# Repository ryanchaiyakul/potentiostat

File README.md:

# Potentiostat

I2BL potentiostat library and project.

# Goals

1. Create a library to easily program simple potentiostats for various voltammetry methods.
2. Create a collection of tools to develop future potentiostats.
3. Create a simulation suite to visualize and validate design decisions.

# Simulations

Go to the [README.md](CAD/LTSpice/README.md) in CAD/LTSpice folder.

# Tools

Go to the tools folder for a complete collection.

## CPE Models

Generate RC Train models of CPE elements to simulate how the readout circuit responds.

## PWL Voltammetry

Generate PWL files to pass into a voltage source to act as the DAC.

# Usage

```bash
# submodules are used in this repository for third party libraries
git clone --recurse-submodules git@github.com:ryanchaiyakul/potentiostat.git
```

1. Open the project in [VS Code](https://code.visualstudio.com/) with the [PlatformIO extension](https://marketplace.visualstudio.com/items?itemName=platformio.platformio-ide) installed.
2. Connect the Potentiostat to your computer by USB.
3. Navigate to the PlatformIO panel and click "Upload" or use the Command Palette (CNTL + SHIFT + P) and select "Upload".
4. Use the Serial Monitor in the terminal bar and select the baudrate of 230400.

# Features

- [x] Differential Pulse Voltammetry
- [x] Square Wave Voltammetry
- [ ] Cyclic Voltammetry
- [x] 300+ Hz SWV
- [ ] OTA Configuration
- [ ] EEPROM Persistent Configuration
- [ ] BLE Integration
- [x] Simple "Debug" Mode
- [x] Complete Analytics in "Debug" Mode
- [ ] Unit Testing Suite

# Development Guide

Create a valid class that inherits from Voltammetry defined in [Voltammetry.h](lib/Voltammetry/Voltammetry.h).

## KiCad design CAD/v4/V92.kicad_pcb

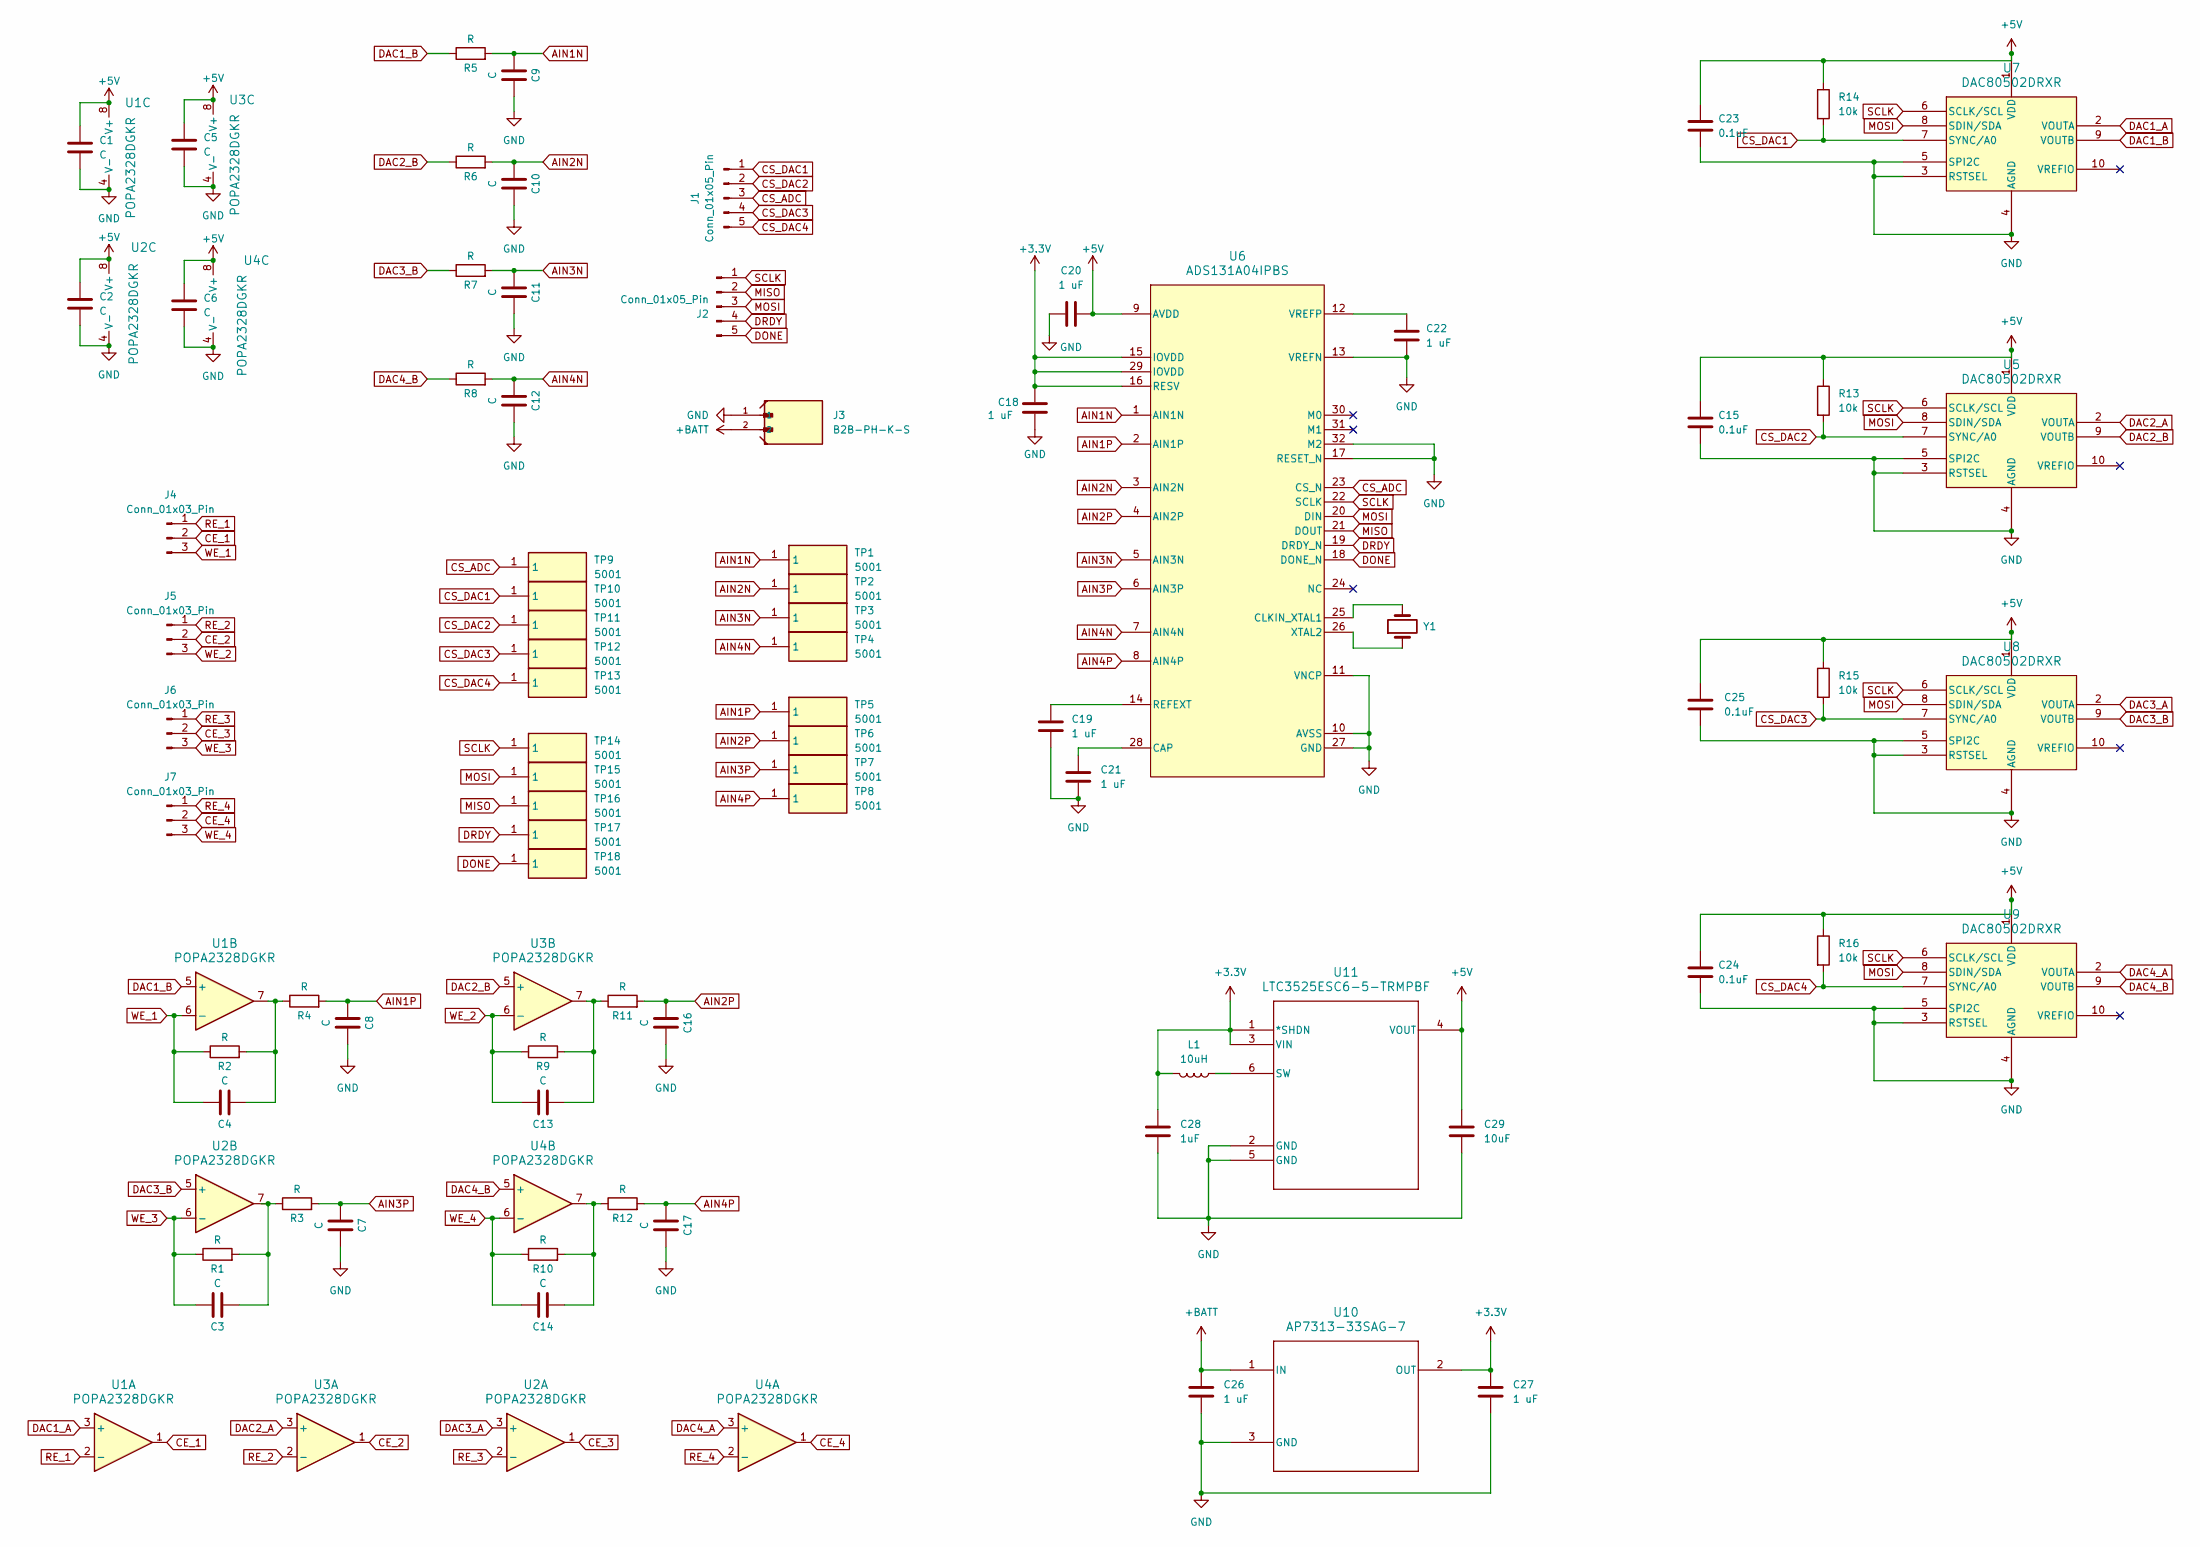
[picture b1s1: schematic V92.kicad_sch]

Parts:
C1, C2, C3, C4, C5, C6, C7, C8, C9, C10, C11, C12, C13, C14, C16, C17: C; C_0603_1608Metric_Pad1.08x0.95mm_HandSolder
C15, C23, C24, C25: 0.1uF; C_0603_1608Metric_Pad1.08x0.95mm_HandSolder
C18, C19, C20, C21, C22, C26, C27: 1 uF; C_0603_1608Metric_Pad1.08x0.95mm_HandSolder
C28: 1uF; C_0603_1608Metric_Pad1.08x0.95mm_HandSolder
C29: 10uF; C_0603_1608Metric_Pad1.08x0.95mm_HandSolder
J1, J2: Conn_01x05_Pin; PinHeader_1x05_P2.54mm_Vertical
J3: B2B-PH-K-S; JST_B2B-PH-K-S
J4, J5, J6, J7: Conn_01x03_Pin; PinHeader_1x03_P2.54mm_Vertical
L1: 10uH; L_0603_1608Metric_Pad1.05x0.95mm_HandSolder
R1, R2, R3, R4, R5, R6, R7, R8, R9, R10, R11, R12: R; R_0603_1608Metric_Pad0.98x0.95mm_HandSolder
R13, R14, R15, R16: 10k; R_0603_1608Metric_Pad0.98x0.95mm_HandSolder
TP1, TP2, TP3, TP4, TP5, TP6, TP7, TP8, TP9, TP10, TP11, TP12, TP13, TP14, TP15, TP16, TP17, TP18: 5001; 5000; Mouser Part Number 534-5001
U1, U2, U3, U4: POPA2328DGKR; SO8_DGK_TEX
U5, U7, U8, U9: DAC80502DRXR; SON_02DRXR_TEX
U6: ADS131A04IPBS; PBS0032A_N
U10: AP7313-33SAG-7; SOT-23_DIO
U11: LTC3525ESC6-5-TRMPBF; SC70-SC6_LIT
Y1: Crystal; Crystal_SMD_HC49-SD

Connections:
+3.3V: C18.1, C27.1, C28.1, L1.2, U6.15 (IOVDD), U6.16 (RESV), U6.29 (IOVDD), U10.2 (OUT), U11.1 (*SHDN), U11.3 (VIN)
+5V: C1.1, C2.1, C5.1, C6.1, C15.1, C20.1, C23.1, C24.1, C25.1, C29.1, R13.1, R14.1, R15.1, R16.1, U1.8 (V+), U2.8 (V+), U3.8 (V+), U4.8 (V+), U5.1 (VDD), U6.9 (AVDD), U7.1 (VDD), U8.1 (VDD), U9.1 (VDD), U11.4 (VOUT)
+BATT: C26.1, J3.2, U10.1 (IN)
AIN1N: C9.2, R5.2, TP1.1, U6.1 (AIN1N)
AIN1P: C8.2, R4.2, TP5.1, U6.2 (AIN1P)
AIN2N: C10.2, R6.2, TP2.1, U6.3 (AIN2N)
AIN2P: C16.2, R11.2, TP6.1, U6.4 (AIN2P)
AIN3N: C11.2, R7.2, TP3.1, U6.5 (AIN3N)
AIN3P: C7.2, R3.2, TP7.1, U6.6 (AIN3P)
AIN4N: C12.2, R8.2, TP4.1, U6.7 (AIN4N)
AIN4P: C17.2, R12.2, TP8.1, U6.8 (AIN4P)
CE_1: J4.2, U1.1
CE_2: J5.2, U3.1
CE_3: J6.2, U2.1
CE_4: J7.2, U4.1
CS_ADC: J1.3, TP9.1, U6.23 (CS_N)
CS_DAC1: J1.1, R14.2, TP10.1, U7.7 (SYNC/A0)
CS_DAC2: J1.2, R13.2, TP11.1, U5.7 (SYNC/A0)
CS_DAC3: J1.4, R15.2, TP12.1, U8.7 (SYNC/A0)
CS_DAC4: J1.5, R16.2, TP13.1, U9.7 (SYNC/A0)
DAC1_A: U1.3 (+), U7.2 (VOUTA)
DAC1_B: R5.1, U1.5 (+), U7.9 (VOUTB)
DAC2_A: U3.3 (+), U5.2 (VOUTA)
DAC2_B: R6.1, U3.5 (+), U5.9 (VOUTB)
DAC3_A: U2.3 (+), U8.2 (VOUTA)
DAC3_B: R7.1, U2.5 (+), U8.9 (VOUTB)
DAC4_A: U4.3 (+), U9.2 (VOUTA)
DAC4_B: R8.1, U4.5 (+), U9.9 (VOUTB)
DONE: J2.5, TP18.1, U6.18 (DONE_N)
DRDY: J2.4, TP17.1, U6.19 (DRDY_N)
GND: C1.2, C2.2, C5.2, C6.2, C7.1, C8.1, C9.1, C10.1, C11.1, C12.1, C15.2, C16.1, C17.1, C18.2, C19.2, C20.2, C21.2, C22.2, C23.2, C24.2, C25.2, C26.2, C27.2, C28.2, C29.2, J3.1, U1.4 (V-), U2.4 (V-), U3.4 (V-), U4.4 (V-), U5.3 (RSTSEL), U5.4 (AGND), U5.5 (SPI2C), U6.10 (AVSS), U6.11 (VNCP), U6.13 (VREFN), U6.17 (RESET_N), U6.27 (GND), U6.32 (M2), U7.3 (RSTSEL), U7.4 (AGND), U7.5 (SPI2C), U8.3 (RSTSEL), U8.4 (AGND), U8.5 (SPI2C), U9.3 (RSTSEL), U9.4 (AGND), U9.5 (SPI2C), U10.3 (GND), U11.2 (GND), U11.5 (GND)
MISO: J2.2, TP16.1, U6.21 (DOUT)
MOSI: J2.3, TP15.1, U5.8 (SDIN/SDA), U6.20 (DIN), U7.8 (SDIN/SDA), U8.8 (SDIN/SDA), U9.8 (SDIN/SDA)
unnamed: C3.2, R1.2, R3.1, U2.7
unnamed: C4.2, R2.2, R4.1, U1.7
unnamed: C13.2, R9.2, R11.1, U3.7
unnamed: C14.2, R10.2, R12.1, U4.7
unnamed: C21.1, U6.28 (CAP)
unnamed: U6.25 (CLKIN_XTAL1), Y1.2
unnamed: C19.1, U6.14 (REFEXT)
unnamed: C22.1, U6.12 (VREFP)
unnamed: U6.26 (XTAL2), Y1.1
unnamed: L1.1, U11.6 (SW)
RE_1: J4.1, U1.2 (-)
RE_2: J5.1, U3.2 (-)
RE_3: J6.1, U2.2 (-)
RE_4: J7.1, U4.2 (-)
SCLK: J2.1, TP14.1, U5.6 (SCLK/SCL), U6.22 (SCLK), U7.6 (SCLK/SCL), U8.6 (SCLK/SCL), U9.6 (SCLK/SCL)
WE_1: C4.1, J4.3, R2.1, U1.6 (-)
WE_2: C13.1, J5.3, R9.1, U3.6 (-)
WE_3: C3.1, J6.3, R1.1, U2.6 (-)
WE_4: C14.1, J7.3, R10.1, U4.6 (-)

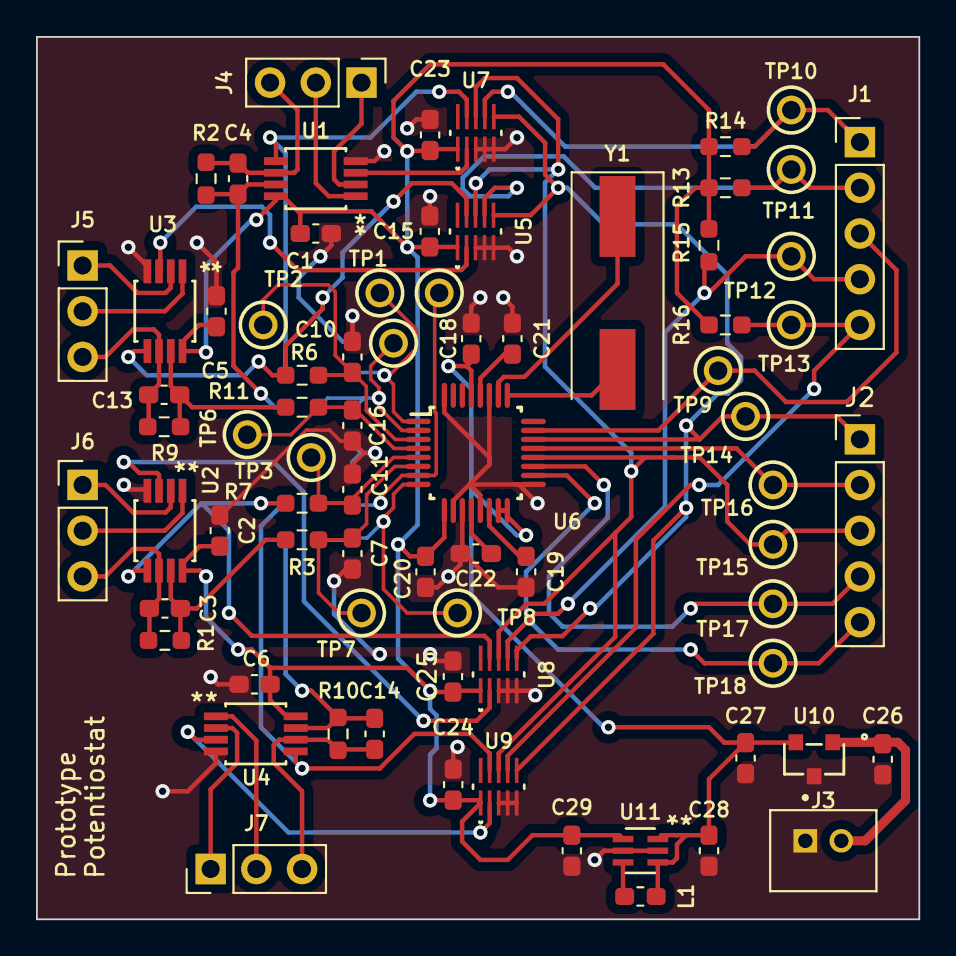
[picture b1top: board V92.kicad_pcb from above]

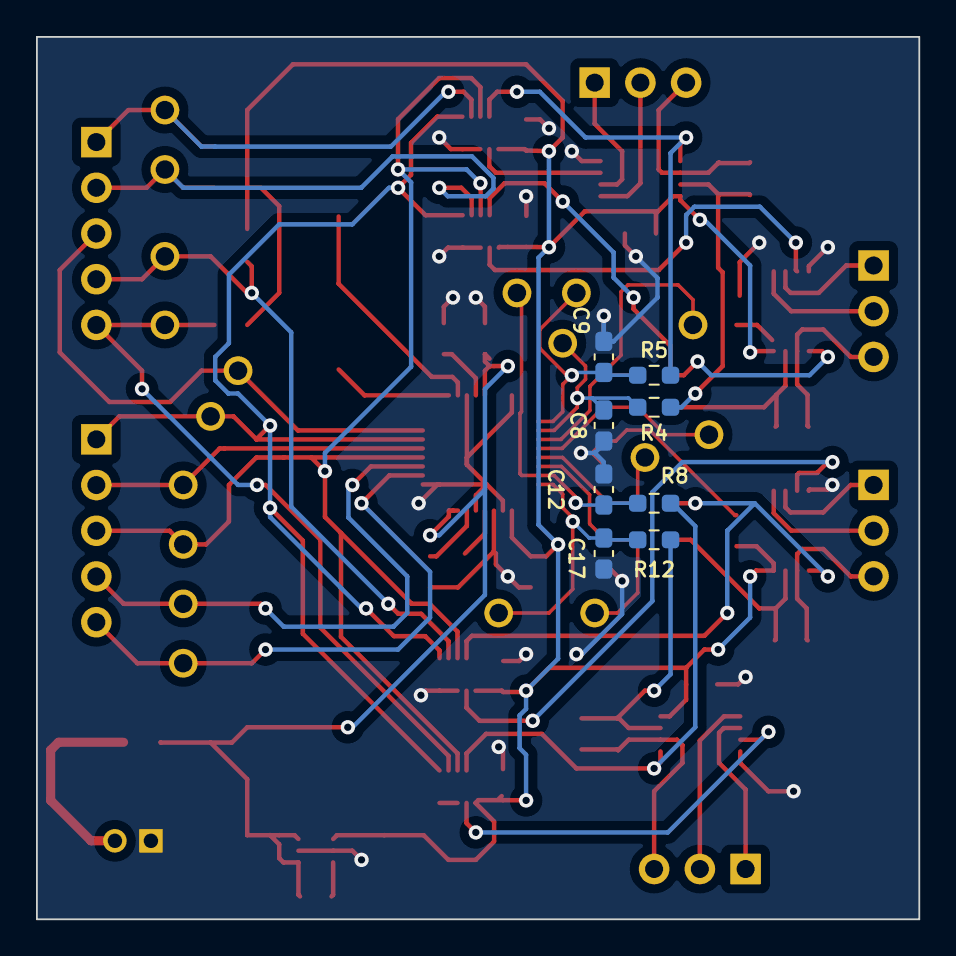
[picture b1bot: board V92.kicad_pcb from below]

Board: 2 copper layers, 49.0 x 49.0 mm, 83 parts (8 on the bottom side), 52 nets.

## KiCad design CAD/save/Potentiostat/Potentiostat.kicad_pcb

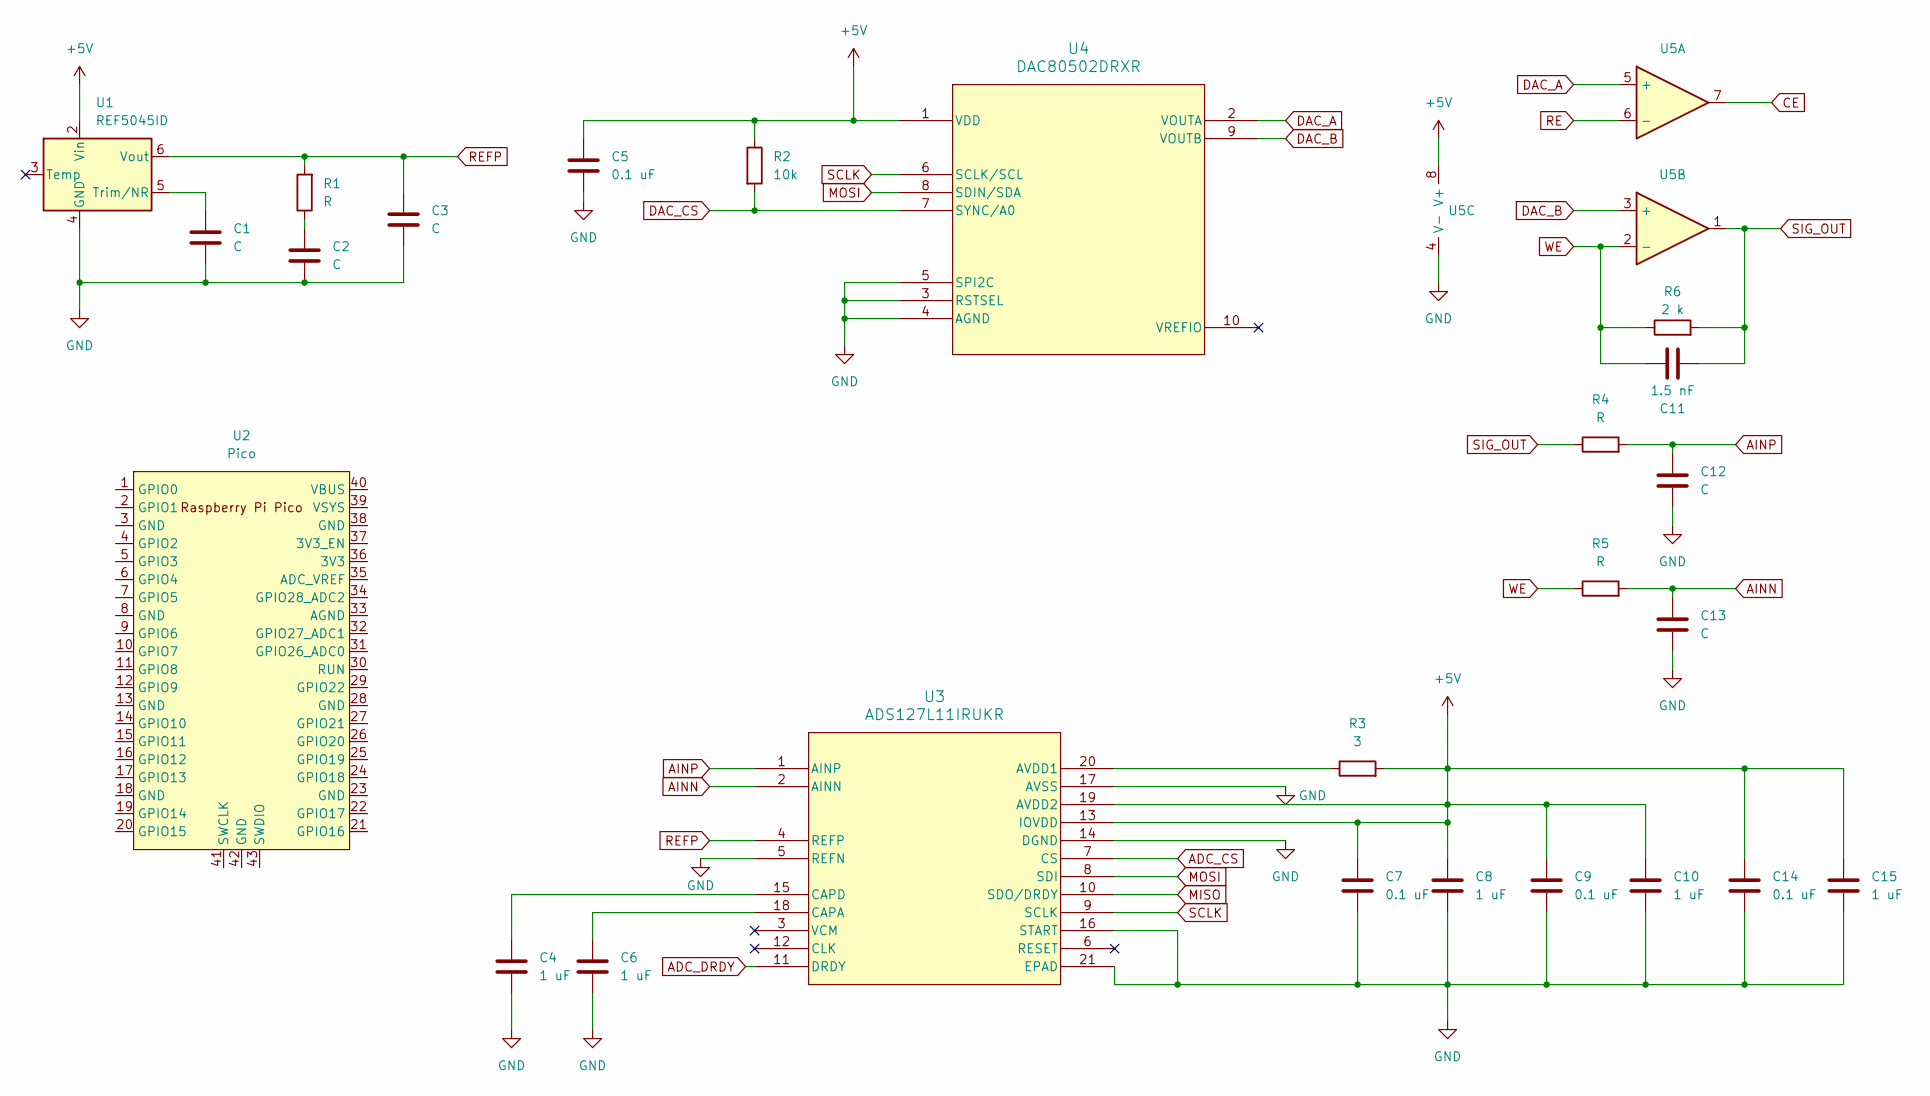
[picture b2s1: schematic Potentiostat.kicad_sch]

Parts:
C1, C2, C3, C12, C13: C; C_0603_1608Metric_Pad1.08x0.95mm_HandSolder
C4, C6, C8, C10, C15: 1 uF; C_0603_1608Metric_Pad1.08x0.95mm_HandSolder
C5, C7, C9, C14: 0.1 uF; C_0603_1608Metric_Pad1.08x0.95mm_HandSolder
C11: 1.5 nF; C_0603_1608Metric_Pad1.08x0.95mm_HandSolder
R1, R4, R5: R; R_0603_1608Metric_Pad0.98x0.95mm_HandSolder
R2: 10k; R_0603_1608Metric_Pad0.98x0.95mm_HandSolder
R3: 3; R_0603_1608Metric_Pad0.98x0.95mm_HandSolder
R6: 2 k; R_0603_1608Metric_Pad0.98x0.95mm_HandSolder
U1: REF5045ID; SOIC-8_3.9x4.9mm_P1.27mm
U2: Pico; RPi_Pico_SMD_TH
U3: ADS127L11IRUKR; WQFN20_RUK_TEX
U4: DAC80502DRXR; SON_02DRXR_TEX
U5: SO8_DGK_TEX

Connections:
+5V: C5.1, C7.1, C8.1, C9.1, C10.1, C14.1, C15.1, R2.1, R3.2, U1.2 (Vin), U3.13 (IOVDD), U3.19 (AVDD2), U4.1 (VDD), U5.8 (V+)
ADC_CS: U3.7 (CS)
ADC_DRDY: U3.11 (DRDY)
AINN: C13.1, R5.2, U3.2 (AINN)
AINP: C12.1, R4.2, U3.1 (AINP)
CE: U5.7
DAC_A: U4.2 (VOUTA), U5.5 (+)
DAC_B: U4.9 (VOUTB), U5.3 (+)
DAC_CS: R2.2, U4.7 (SYNC/A0)
GND: C1.2, C2.2, C3.2, C4.2, C5.2, C6.2, C7.2, C8.2, C9.2, C10.2, C12.2, C13.2, C14.2, C15.2, U1.4 (GND), U3.5 (REFN), U3.14 (DGND), U3.16 (START), U3.17 (AVSS), U3.21 (EPAD), U4.3 (RSTSEL), U4.4 (AGND), U4.5 (SPI2C), U5.4 (V-)
MISO: U3.10 (SDO/DRDY)
MOSI: U3.8 (SDI), U4.8 (SDIN/SDA)
unnamed: C2.1, R1.1
unnamed: C1.1, U1.5 (Trim/NR)
unnamed: R3.1, U3.20 (AVDD1)
unnamed: C6.1, U3.18 (CAPA)
unnamed: C4.1, U3.15 (CAPD)
RE: U5.6 (-)
REFP: C3.1, R1.2, U1.6 (Vout), U3.4 (REFP)
SCLK: U3.9 (SCLK), U4.6 (SCLK/SCL)
SIG_OUT: C11.1, R4.1, R6.2, U5.1
WE: C11.2, R5.1, R6.1, U5.2 (-)

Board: 2 copper layers, 26 parts (0 on the bottom side), 17 nets, no tracks yet.

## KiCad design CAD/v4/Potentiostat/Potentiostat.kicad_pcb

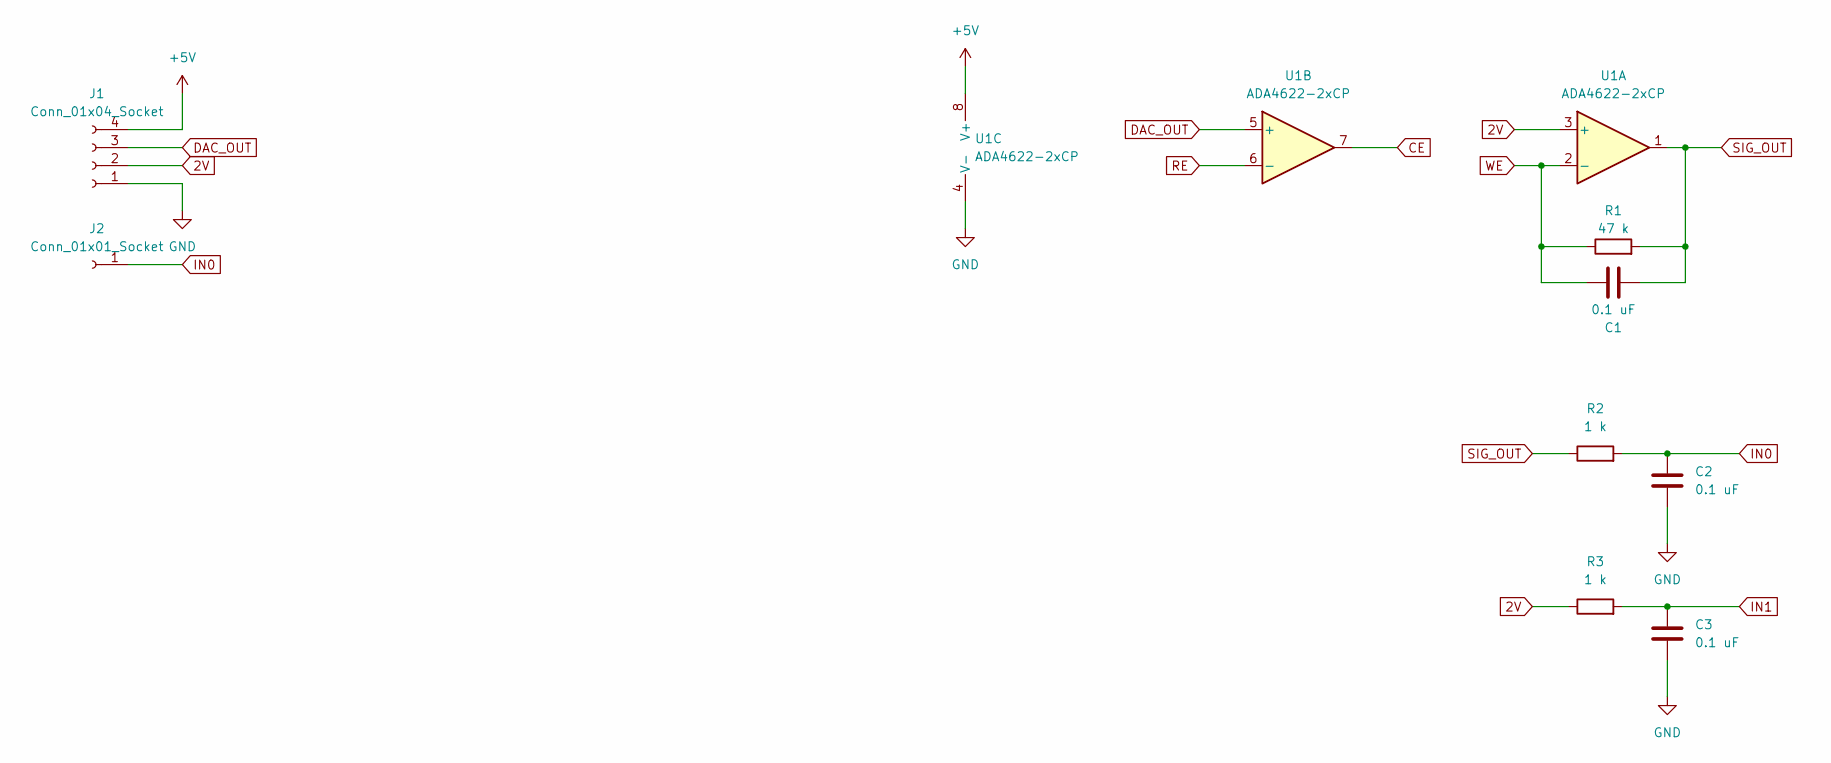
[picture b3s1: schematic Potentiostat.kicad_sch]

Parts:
C1, C2, C3: 0.1 uF; C_0603_1608Metric_Pad1.08x0.95mm_HandSolder
J1: Conn_01x04_Socket; PinHeader_1x04_P1.00mm_Vertical
J2: Conn_01x01_Socket; PinHeader_1x01_P1.00mm_Vertical
R1: 47 k; R_0603_1608Metric_Pad0.98x0.95mm_HandSolder
R2, R3: 1 k; R_0603_1608Metric_Pad0.98x0.95mm_HandSolder
U1: ADA4622-2xCP; LFCSP-8-1EP_3x3mm_P0.5mm_EP1.45x1.74mm

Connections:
2V: J1.2, R3.1, U1.3 (+)
+5V: J1.4, U1.8 (V+), U1.9 (V+)
CE: U1.7
DAC_OUT: J1.3, U1.5 (+)
GND: C2.2, C3.2, J1.1, U1.4 (V-)
IN0: C2.1, J2.1, R2.2
IN1: C3.1, R3.2
RE: U1.6 (-)
SIG_OUT: C1.1, R1.2, R2.1, U1.1
WE: C1.2, R1.1, U1.2 (-)

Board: 2 copper layers, 9 parts (0 on the bottom side), 8 nets, no tracks yet.

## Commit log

2023-08-09 initial commit
    working DPV
2023-08-09 somewhat working version
2023-08-11 working swv and dpv
2023-08-15 added settings
2023-08-15 switched to nonblocking design
2023-08-18 working copy
2023-08-18 basic readme
2023-08-18 fixed minor comments
2023-08-21 renamed .ino file
    Arduino IDE does not like files not named after the folder they are in
2023-08-21 added testing suite
    Still need to make comments and refine
2023-08-23 working 30k sps ADC
2023-08-25 working master with 30k SPS
2023-08-25 added .ipynb
2023-10-21 initial commit
    Working DPV and SWV configured by fixed variables. Contains basic
    LTSpice for TransAmp calculations. Use with VS Code and Platform.io.
2023-10-21 documentation
    Created README.md for the overall project
2023-10-21 CAD populated
    Moved transAmp into folder and brought back v3 Eagle design
2023-10-21 Update platformio.yml
    Added submodules
2023-10-21 Update platformio.yml
    round 2 of submodules
2023-10-21 Update README.md
    Added markdown badge for CI
2024-01-08 starting transamp
2024-01-12 migrated LTSpice files
    Moved and renamed LTSpice files into corresponding folder with .plt
    forms
2024-04-09 working DAC80502
    The SPI works but it is intermittent
2024-04-13 cleaned up workspace
    Added documentation and finalized folder structure
2024-04-13 removed excess import guides
2024-04-26 pushing wip LMP910000
2024-12-16 final
2025-01-31 add CPE back
